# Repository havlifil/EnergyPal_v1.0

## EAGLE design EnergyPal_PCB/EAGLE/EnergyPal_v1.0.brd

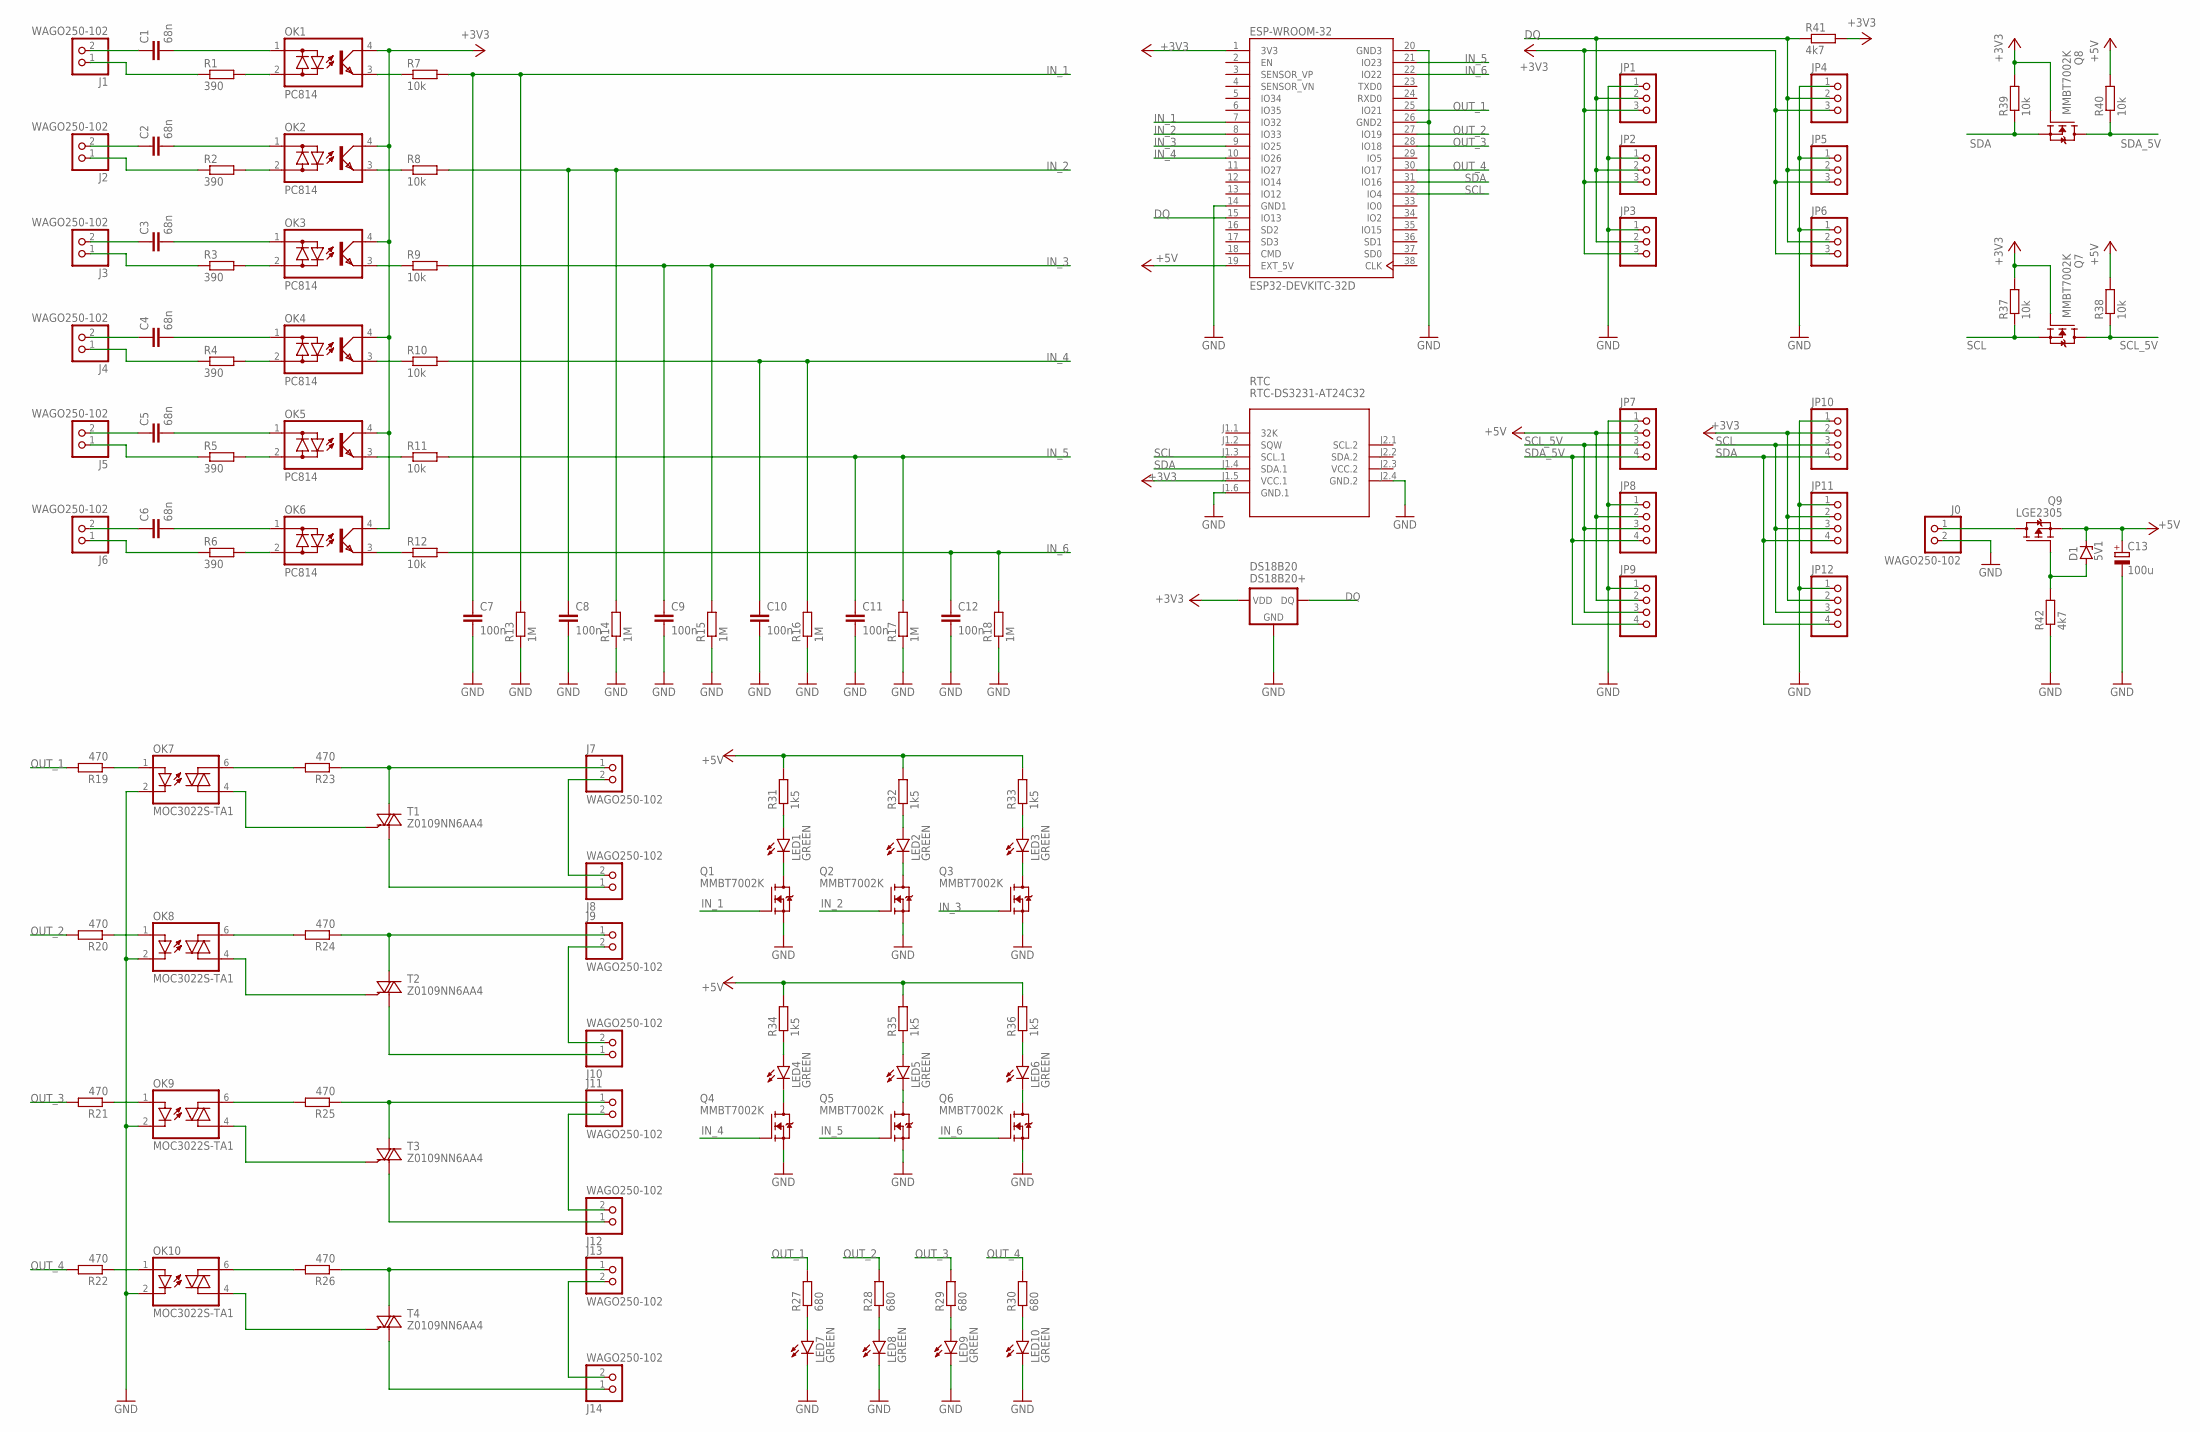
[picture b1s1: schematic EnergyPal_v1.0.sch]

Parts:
C1, C2, C3, C4, C5, C6: 68n; C075-063X106
C7, C8, C9, C10, C11, C12: 100n; C1206
C13: 100u; UD-6,3X7,7_NICHICON
D1: 5V1; SOD123
DS18B20: DS18B20+; TO92-
ESP-WROOM-32: ESP32-DEVKITC-32D; MODULE_ESP32-DEVKITC-32D
J0, J1, J2, J3, J4, J5, J6, J7, J8, J9, J10, J11, J12, J13, J14: WAGO250-102; 250102
JP1, JP2, JP3, JP4, JP5, JP6: PINHD-1X3; 1X03
JP7, JP8, JP9, JP10, JP11, JP12: PINHD-1X4; 1X04
LED1, LED2, LED3, LED4, LED5, LED6, LED7, LED8, LED9, LED10: GREEN; 1206
OK1, OK2, OK3, OK4, OK5, OK6: PC814; SOP254P960X420-4N
OK7, OK8, OK9, OK10: MOC3022S-TA1; SOP254P1016X460-6N
Q1, Q2, Q3, Q4, Q5, Q6, Q7, Q8: MMBT7002K; SOT23
Q9: LGE2305; SOT23
R1, R2, R3, R4, R5, R6: 390; R1206
R7, R8, R9, R10, R11, R12, R37, R38, R39, R40: 10k; R1206
R13, R14, R15, R16, R17, R18: 1M; R1206
R19, R20, R21, R22, R23, R24, R25, R26: 470; R1206
R27, R28, R29, R30: 680; R1206
R31, R32, R33, R34, R35, R36: 1k5; R1206
R41, R42: 4k7; R1206
RTC: RTC-DS3231-AT24C32; RTC-DS3231-AT24C32#MIRROR
T1, T2, T3, T4: Z0109NN6AA4; SOT230P700X190-4N

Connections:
+3V3: DS18B20.3 (VDD), ESP-WROOM-32.1 (3V3), JP1.3, JP2.3, JP3.3, JP4.3, JP5.3, JP6.3, JP10.2, JP11.2, JP12.2, OK1.4 (C), OK2.4 (C), OK3.4 (C), OK4.4 (C), OK5.4 (C), OK6.4 (C), Q7.1 (G), Q8.1 (G), R37.2, R39.2, R41.2, RTC.J1.5 (VCC.1)
+5V: C13.+, D1.C, ESP-WROOM-32.19 (EXT_5V), JP7.2, JP8.2, JP9.2, Q9.2 (S), R31.2, R32.2, R33.2, R34.2, R35.2, R36.2, R38.2, R40.2
DQ: DS18B20.2 (DQ), ESP-WROOM-32.15 (IO13), JP1.2, JP2.2, JP3.2, JP4.2, JP5.2, JP6.2, R41.1
GND: C7.2, C8.2, C9.2, C10.2, C11.2, C12.2, C13.-, DS18B20.1 (GND), ESP-WROOM-32.14 (GND1), ESP-WROOM-32.20 (GND3), ESP-WROOM-32.26 (GND2), J0.2, JP1.1, JP2.1, JP3.1, JP4.1, JP5.1, JP6.1, JP7.1, JP8.1, JP9.1, JP10.1, JP11.1, JP12.1, LED7.C, LED8.C, LED9.C, LED10.C, OK7.2 (C), OK8.2 (C), OK9.2 (C), OK10.2 (C), Q1.2 (S), Q2.2 (S), Q3.2 (S), Q4.2 (S), Q5.2 (S), Q6.2 (S), R13.1, R14.1, R15.1, R16.1, R17.1, R18.1, R42.1, RTC.J1.6 (GND.1), RTC.J2.4 (GND.2)
IN_1: C7.1, ESP-WROOM-32.7 (IO32), Q1.1 (G), R7.2, R13.2
IN_2: C8.1, ESP-WROOM-32.8 (IO33), Q2.1 (G), R8.2, R14.2
IN_3: C9.1, ESP-WROOM-32.9 (IO25), Q3.1 (G), R9.2, R15.2
IN_4: C10.1, ESP-WROOM-32.10 (IO26), Q4.1 (G), R10.2, R16.2
IN_5: C11.1, ESP-WROOM-32.21 (IO23), Q5.1 (G), R11.2, R17.2
IN_6: C12.1, ESP-WROOM-32.22 (IO22), Q6.1 (G), R12.2, R18.2
unnamed: C1.1, J1.2
unnamed: C1.2, OK1.1 (AC1)
unnamed: OK6.2 (AC2), R6.2
unnamed: J6.1, R6.1
unnamed: C2.1, J2.2
unnamed: C2.2, OK2.1 (AC1)
unnamed: J2.1, R2.1
unnamed: OK2.2 (AC2), R2.2
unnamed: OK4.3 (E), R10.1
unnamed: OK3.3 (E), R9.1
unnamed: OK2.3 (E), R8.1
unnamed: OK1.3 (E), R7.1
unnamed: OK7.1 (A), R19.1
unnamed: OK7.6 (A2), R23.2
unnamed: OK8.1 (A), R20.1
unnamed: J1.1, R1.1
unnamed: OK8.6 (A2), R24.2
unnamed: OK1.2 (AC2), R1.2
unnamed: C3.1, J3.2
unnamed: J9.1, R24.1, T2.2 (A2), T2.4 (A2)
unnamed: OK8.4 (A1), T2.3 (G)
unnamed: J10.1, T2.1 (A1)
unnamed: J9.2, J10.2
unnamed: J0.1, Q9.3 (D)
unnamed: C3.2, OK3.1 (AC1)
unnamed: OK9.1 (A), R21.1
unnamed: J7.2, J8.2
unnamed: OK9.6 (A2), R25.2
unnamed: J3.1, R3.1
unnamed: OK3.2 (AC2), R3.2
unnamed: J11.1, R25.1, T3.2 (A2), T3.4 (A2)
unnamed: OK9.4 (A1), T3.3 (G)
unnamed: C4.1, J4.2
unnamed: C4.2, OK4.1 (AC1)
unnamed: J4.1, R4.1
unnamed: OK4.2 (AC2), R4.2
unnamed: C5.1, J5.2
unnamed: C5.2, OK5.1 (AC1)
unnamed: J5.1, R5.1
unnamed: LED1.C, Q1.3 (D)
unnamed: D1.A, Q9.1 (G), R42.2
unnamed: LED7.A, R27.1
unnamed: LED1.A, R31.1
unnamed: LED2.A, R32.1
unnamed: LED2.C, Q2.3 (D)
unnamed: LED8.A, R28.1
unnamed: LED3.A, R33.1
unnamed: LED3.C, Q3.3 (D)
unnamed: OK5.2 (AC2), R5.2
unnamed: LED9.A, R29.1
unnamed: C6.1, J6.2
unnamed: OK5.3 (E), R11.1
unnamed: C6.2, OK6.1 (AC1)
unnamed: OK6.3 (E), R12.1
unnamed: LED4.A, R34.1
unnamed: LED4.C, Q4.3 (D)
unnamed: LED10.A, R30.1
unnamed: LED5.A, R35.1
unnamed: LED5.C, Q5.3 (D)
unnamed: J7.1, R23.1, T1.2 (A2), T1.4 (A2)
unnamed: LED6.A, R36.1
unnamed: LED6.C, Q6.3 (D)
unnamed: OK7.4 (A1), T1.3 (G)
unnamed: J8.1, T1.1 (A1)
unnamed: J12.1, T3.1 (A1)
unnamed: J11.2, J12.2
unnamed: OK10.1 (A), R22.1
unnamed: OK10.6 (A2), R26.2
unnamed: J13.1, R26.1, T4.2 (A2), T4.4 (A2)
unnamed: OK10.4 (A1), T4.3 (G)
unnamed: J14.1, T4.1 (A1)
unnamed: J13.2, J14.2
OUT_1: ESP-WROOM-32.25 (IO21), R19.2, R27.2
OUT_2: ESP-WROOM-32.27 (IO19), R20.2, R28.2
OUT_3: ESP-WROOM-32.28 (IO18), R21.2, R29.2
OUT_4: ESP-WROOM-32.30 (IO17), R22.2, R30.2
SCL: ESP-WROOM-32.32 (IO4), JP10.3, JP11.3, JP12.3, Q7.2 (S), R37.1, RTC.J1.3 (SCL.1)
SCL_5V: JP7.3, JP8.3, JP9.3, Q7.3 (D), R38.1
SDA: ESP-WROOM-32.31 (IO16), JP10.4, JP11.4, JP12.4, Q8.2 (S), R39.1, RTC.J1.4 (SDA.1)
SDA_5V: JP7.4, JP8.4, JP9.4, Q8.3 (D), R40.1
VCC.2: RTC.J2.3 (VCC.2)

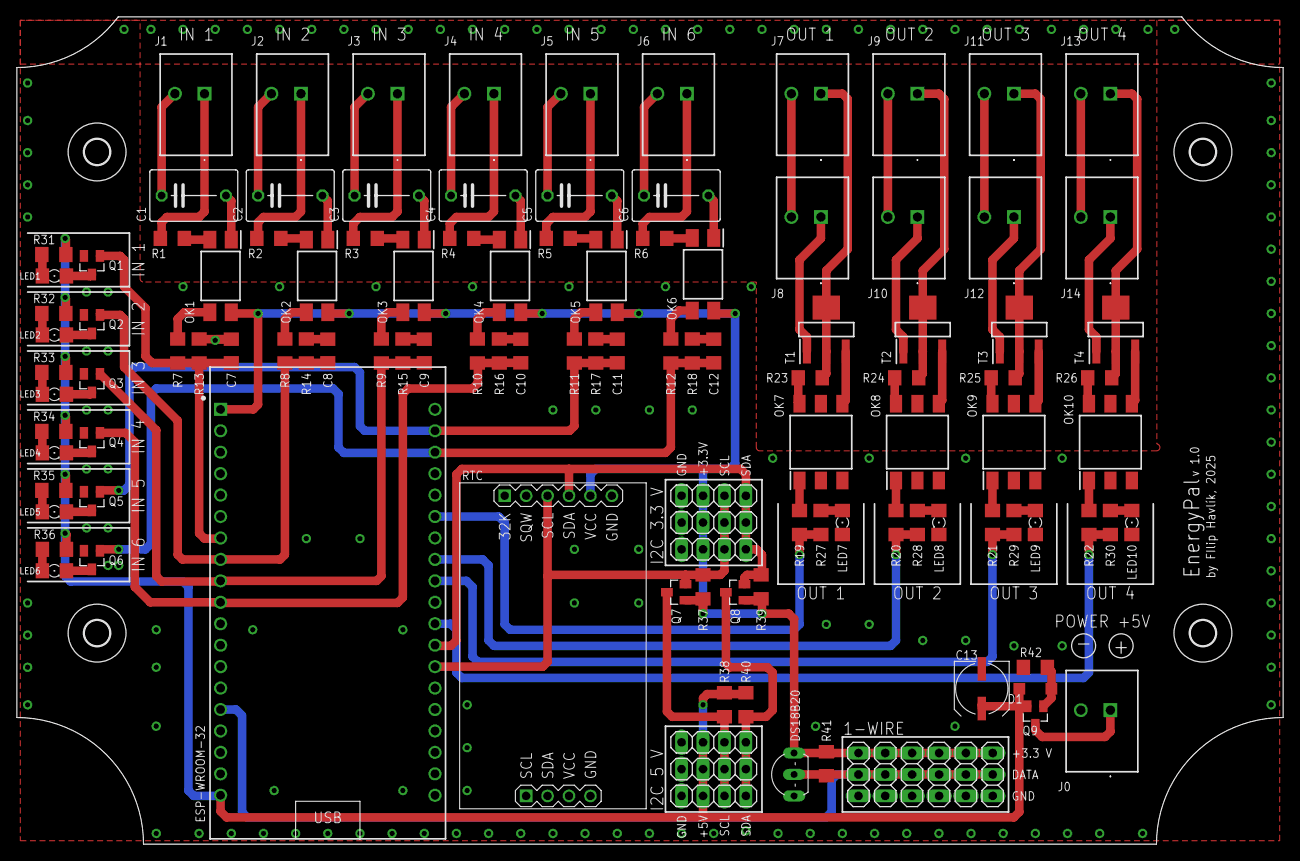
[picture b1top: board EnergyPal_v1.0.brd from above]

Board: 2 copper layers, 150.0 x 98.0 mm, 123 parts (0 on the bottom side), 90 nets.

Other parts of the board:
U$8, U$9, U$10, U$11: 3,0

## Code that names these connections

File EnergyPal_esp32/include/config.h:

#ifndef CONFIG_H
#define CONFIG_H

#include <stdint.h>
#include <DallasTemperature.h>

// declare ID of this device
extern const char* ENERGYPAL_ID;

// WiFi connection info
extern const char* WIFI_SSID;
extern const char* WIFI_PASSWORD;

// website data handler URL
extern const char* MEASUREMENTS_HANDLER_URL;
extern const char* STATES_HANDLER_URL;

// web socket connection info
extern const char* WS_HOST;
extern const char* WS_PATH;
extern const uint16_t WS_PORT;

// declare sensors addrresses
extern const DeviceAddress electricBoilerThermometer;
extern const DeviceAddress gasBoilerThermometer;
extern const DeviceAddress outsideThermometer;
extern const DeviceAddress energyPalThermometer;
extern const DeviceAddress pumpPipeThermometer;
extern const DeviceAddress gasHeaterOut;

// define ESP-WROOM-32 pins
#define pin_IN_1 32
#define pin_IN_2 33
#define pin_IN_3 25
#define pin_IN_4 26
#define pin_IN_5 23
#define pin_IN_6 22
#define pin_OUT_1 21
#define pin_OUT_2 19
#define pin_OUT_3 18
#define pin_OUT_4 17
#define pin_SDA 16
#define pin_SCL 4
#define pin_DQ 13

#define WIFI_TIMEOUT 5000 // define wifi timeout [ms]
#define UDP_PORT 9999 // define UDP port

#define LIMIT_UNSENT_IN_PAYLOAD 100 // limit how much unsent data could be added to the payload (prevent memory overflow)
#define PUMP_TEMP_DIFFERENCE_TRIG 5.0f // difference between temperatures in electric and gas boiler, that triggers pump
#define PUMP_ON_DURATION 20*60 // duration in seconds of pump on states

#endif

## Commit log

2025-04-07 WebSocket

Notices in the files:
parts and their libraries:
diy-modules: Released under the Creative Commons Attribution 4.0 International License: http://creativecommons.org/licenses/by/4.0
